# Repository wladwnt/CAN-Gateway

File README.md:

# CAN-Gateway for Hoval devices (TopTronic&reg; E series)
DEUTSCH: [Wiki](https://github.com/wladwnt/CAN-Gateway/wiki/Deutsche-Wiki) |  [Detailierte Bedienungsanleitung](https://raw.githubusercontent.com/wladwnt/CAN-Gateway/master/Bedienungsanleitung.pdf) | [Zum CAN-Gateway in 7 Schritten](https://github.com/wladwnt/CAN-Gateway/wiki/Schritte-zum-CAN-Gateway) | [Video dazu](https://youtu.be/HU5wEv3FgdE)

ENGLISH: [Wiki](https://github.com/wladwnt/CAN-Gateway/wiki/English-Wiki) |  [Detailed operating manual](https://raw.githubusercontent.com/wladwnt/CAN-Gateway/master/Operating_manual.pdf) | [7 steps to CAN-Gateway](https://github.com/wladwnt/CAN-Gateway/wiki/Steps-to-CAN-Gateway) | [Intro video](https://youtu.be/7HJrZkuCv4k)

Fragen? / Questions? Please contact me via Email: info@myhome-control.de. (I usually answer within of 24 h. Please check your spam folder if you dont receive an answer)

What you need:
 - CAN - Gateway dev board from [MyHome-Control Shop](https://shop.myhome-control.de/CAN-Gateway-development-board/HW10018) (Germany) with optional [housing](https://shop.myhome-control.de/Gehaeuse-fuer-CAN-Gateway-Boards/ZB10001) or board + housing from [WLED SHOP](https://wled.shop/produkt/wladis-can-gateway/) (worldwide shipment). If you have HomeVent with analogue control module (type BG02E with two rotary encoders), please order the CAN-Gateway board version with second CAN interface to be able to use the control module in parallel with CAN-Gateway.
 - CAN - Gateway Software from [MyHome-Control Shop](https://shop.myhome-control.de/CAN-Gateway-Software/SW10000.1)

When you buy the software, you will additionally get access to the [CAN-Gateway online services](https://can-gateway.myhome-control.de/api/) where you can find for example SW updates and the extended database of available parameters.

Android app:  Also in Amazon AppStore: [Link](http://www.amazon.com/gp/mas/dl/android?asin=B099S815PD).

Windows App: [Download Installer](https://raw.githubusercontent.com/wladwnt/CAN-Gateway/master/App/WindowsApp/MyHomeAppSetup_Windows10_x64_v1.1.0.exe)

Bisher getestet mit: TTE-HV (HomeVent), TTE-WEZ (Wärmeerzeuger, wie Wärmepumpe), TTE-HKW (Heizkreis/Warmwasser), TTE-PS (Puffermodul), TTE-SOL (Solar), TTE-BM (Raumbedienmodul), TTE-GW (Gateway), TTE-FW (Fernwärme).

Hier ist die Software nur als eine sogenannte "Demo-Version" in kompilierter Form veröffentlicht. Diese hat im Vergleich zur vollen Version einige Einschränkungen (für Details siehe Bedienungsanleitung, Kapitel "Einschränkungen der Demo-Version").

## Einige Bilder/Screenshots:

Screenshots WEB-Interface:

Author: Dr.-Ing. Wladislaw Waag

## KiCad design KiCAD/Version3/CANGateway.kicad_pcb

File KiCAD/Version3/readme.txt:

Version 3: with SD-Card and RTC, just PCB, no SW support yet.

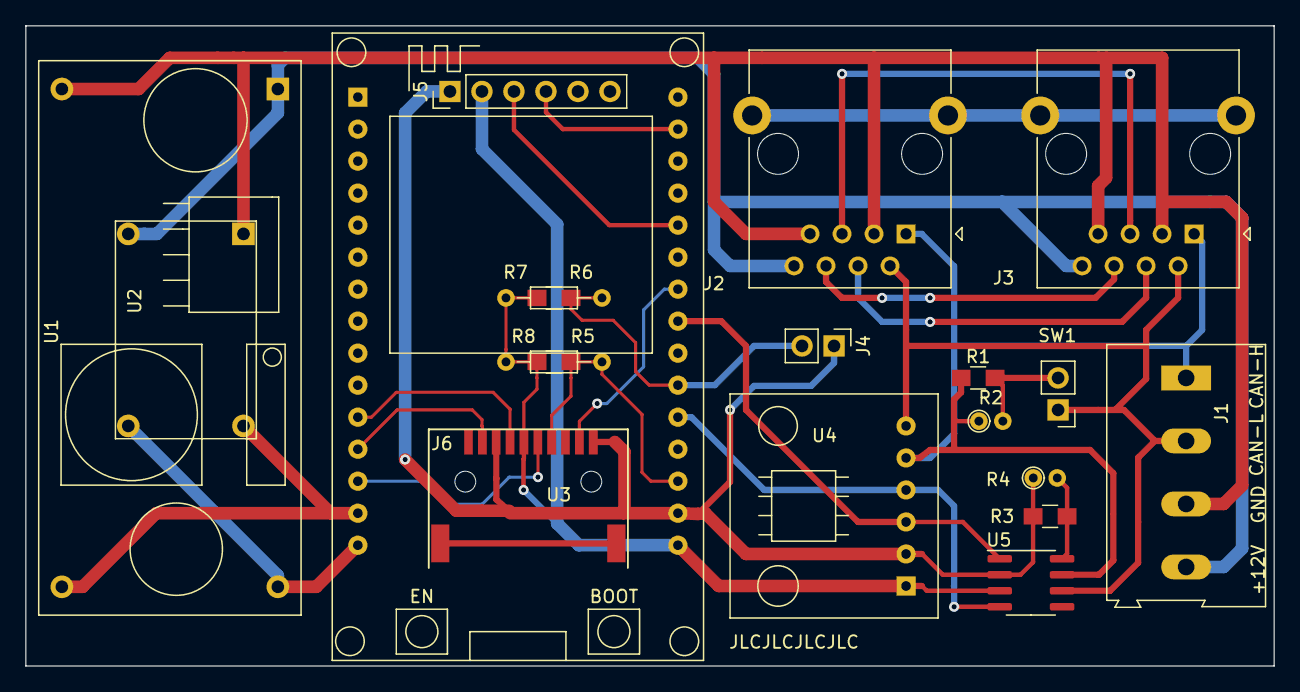
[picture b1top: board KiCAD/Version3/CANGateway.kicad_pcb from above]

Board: 2 copper layers, 99.1 x 50.8 mm, 20 parts (0 on the bottom side), 24 nets.

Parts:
J1: Conn_01x04_Male; TerminalBlock_Altech_AK300-4_P5.00mm
J2, J3: RJ45_Shielded; RJ45_Ninigi_GE
J4: Conn_01x02_Male; Pin_Header_Straight_1x02_Pitch2.54mm
J5: Conn_01x06_Female; Pin_Header_Straight_1x06_Pitch2.54mm
J6: Micro_SD_Card_Det; MicroSd
R1: 120; R_0805_HandSoldering
R2: 120; R_Axial_DIN0204_L3.6mm_D1.6mm_P1.90mm_Vertical
R3, R5, R6: 10k; R_0805_HandSoldering
R4: 10k; R_Axial_DIN0204_L3.6mm_D1.6mm_P1.90mm_Vertical
R7, R8: 10k; R_Axial_DIN0204_L3.6mm_D1.6mm_P7.62mm_Horizontal
SW1: SW_DIP_x01; Pin_Header_Straight_1x02_Pitch2.54mm
U1: LM2596_Module
U2: Mini360_Module
U3: ESP32_DEVKIT1; ESP32_DEVKIT
U4: SN65HVD230_Module
U5: SN65HVD230; SOIC-8_3.9x4.9mm_P1.27mm

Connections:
unnamed: J1.1, J2.1, J3.1, R1.1, R2.1, U4.5, U5.7
unnamed: J1.2, J2.2, J3.2, SW1.1, U4.6, U5.6
unnamed: J1.3, J2.3, J2.7, J3.3, J3.7, U1.2, U2.1
unnamed: J1.4, J2.8, J3.8, U1.1, U2.2
unnamed: J2.4, J3.4
unnamed: J2.5, J3.5
unnamed: J2.6, J3.6
unnamed: J2.SH, J3.SH
unnamed: J4.1, J5.1, J6.6, J6.9, R3.1, R4.1, U3.29, U4.2, U5.2
unnamed: J4.2, R6.2, R7.2, U3.25
unnamed: J5.2, J6.4, R5.2, R6.1, R7.1, R8.2, U3.30, U4.1, U5.3
unnamed: J5.3, U3.20
unnamed: J5.4, U3.17
unnamed: J6.2, R5.1, R8.1, U3.28
unnamed: J6.3, U3.13
unnamed: J6.5, U3.11
unnamed: J6.7, U3.12
unnamed: J6.10, U3.22
unnamed: R1.2, R2.2, SW1.2
unnamed: R3.2, R4.2, U5.8
unnamed: U1.3, U2.4, U3.15
unnamed: U1.4, U2.3, U3.14
unnamed: U3.23, U4.3, U5.1
unnamed: U3.26, U4.4, U5.4

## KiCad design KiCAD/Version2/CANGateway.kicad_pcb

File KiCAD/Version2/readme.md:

2. Version: alternative Bestückungsoptionen für CAN-Transceiver und DC/DC Wandler.

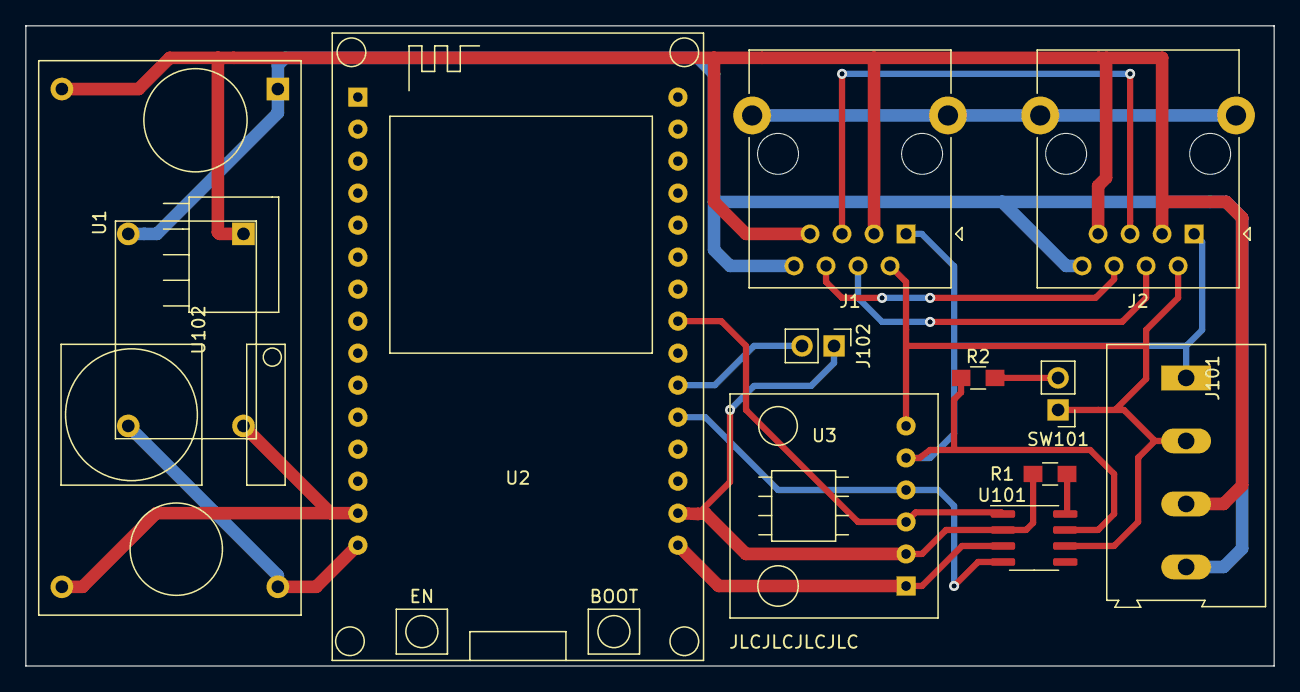
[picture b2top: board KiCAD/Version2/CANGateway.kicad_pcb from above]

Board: 2 copper layers, 99.1 x 50.8 mm, 12 parts (0 on the bottom side), 17 nets.

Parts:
J1, J2: RJ45_Shielded; RJ45_Ninigi_GE
J101: Conn_01x04_Male; TerminalBlock_Altech_AK300-4_P5.00mm
J102: Conn_01x02_Male; Pin_Header_Straight_1x02_Pitch2.54mm
R1: 10k; R_0805_HandSoldering
R2: 120; R_0805_HandSoldering
SW101: SW_DIP_x01; Pin_Header_Straight_1x02_Pitch2.54mm
U1: LM2596_Module
U2: ESP32_DEVKIT1; ESP32_DEVKIT
U3: SN65HVD230_Module
U101: SN65HVD230; SOIC-8_3.9x4.9mm_P1.27mm
U102: Mini360_Module

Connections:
unnamed: J1.1, J2.1, J101.1, R2.1, U3.5, U101.7
unnamed: J1.2, J2.2, J101.2, SW101.1, U3.6, U101.6
unnamed: J1.3, J1.7, J2.3, J2.7, J101.3, U1.2, U102.1
unnamed: J1.4, J2.4
unnamed: J1.5, J2.5
unnamed: J1.6, J2.6
unnamed: J1.8, J2.8, J101.4, U1.1, U102.2
unnamed: J1.SH, J2.SH
unnamed: J102.1, R1.1, U2.29, U3.2, U101.2
unnamed: J102.2, U2.25
unnamed: R1.2, U101.8
unnamed: R2.2, SW101.2
unnamed: U1.3, U2.15, U102.4
unnamed: U1.4, U2.14, U102.3
unnamed: U2.23, U3.3, U101.1
unnamed: U2.30, U3.1, U101.3
unnamed: U2.26, U3.4, U101.4

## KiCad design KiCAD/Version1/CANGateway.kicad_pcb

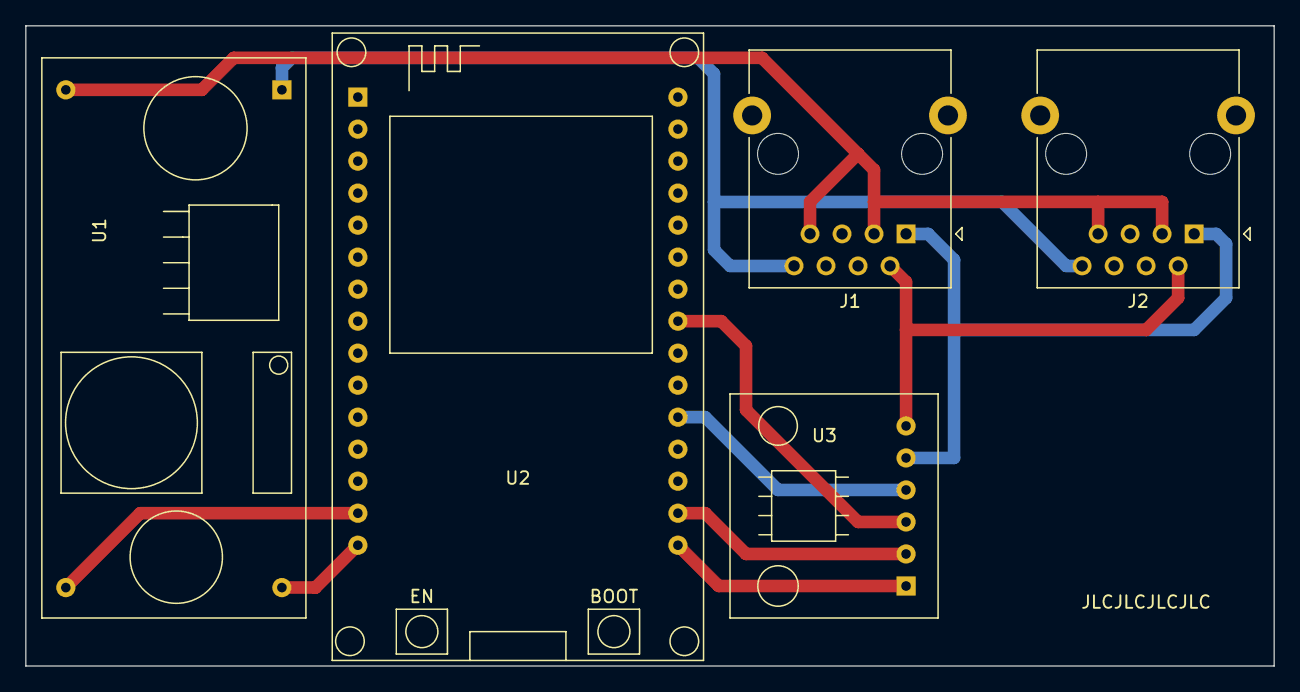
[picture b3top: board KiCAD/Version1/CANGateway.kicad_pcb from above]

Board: 2 copper layers, 99.1 x 50.8 mm, 5 parts (0 on the bottom side), 10 nets.

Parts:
J1, J2: RJ45_Shielded; RJ45_Ninigi_GE
U1: LM2596_Module
U2: ESP32_DEVKIT1; ESP32_DEVKIT
U3: SN65HVD230_Module

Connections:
unnamed: J1.1, J2.1, U3.5
unnamed: J1.2, J2.2, U3.6
unnamed: J1.3, J1.7, J2.3, J2.7, U1.2
unnamed: J1.8, J2.8, U1.1
unnamed: U1.3, U2.15
unnamed: U1.4, U2.14
unnamed: U2.23, U3.3
unnamed: U2.26, U3.4
unnamed: U2.29, U3.2
unnamed: U2.30, U3.1

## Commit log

2020-03-22 Corrected HW (GND Pin)
2020-03-22 HW correction (GND Pin3 on RJ45)
2020-10-07 Klarstellung bzgl. GND Pins.
    Die beste Lösung ist wohl beide Pins (3 und 7 am RJ45) mit GND zu verbinden.
2020-10-25 Einige Ergänzungen / Some additional information
2020-10-25 Add some useful infromation
2021-01-01 Update to SW 21.002, (2021)
2021-01-12 Rename readme.txt to readme.md
2021-03-29 Update SW to 27.100 (SD card and BG02E Support)
2021-07-31 SW Version 28.100 / Android App 1.1
2021-07-31 SW V 28.100 / App V 1.1
2021-08-03 SW 28.100 / App V1.1
2021-08-11 Flasher V1.0
2021-08-11 V2.0
2021-08-19 Update 4: Windows App added
2021-08-24 V28.100 / App 1.1.1
2021-09-10 SW 29.001 / App 1.1.1; KNX IP introduced
2021-12-30 Update documentation
2022-06-21 HAS MQTT examples adapted to Home Assistant release 2022.06
2022-07-01 KNX update
